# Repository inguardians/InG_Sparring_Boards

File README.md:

InG_Sparring_Boards
===================

InGuardians Sparring Boards - a collection of printed circuit boards (PCB) to help users learn about embedded devices and the tools and techniques used during development and assessment.

InGuardians<br>
http://www.inguardians.com<br>
http://labs.inguardians.com<br>

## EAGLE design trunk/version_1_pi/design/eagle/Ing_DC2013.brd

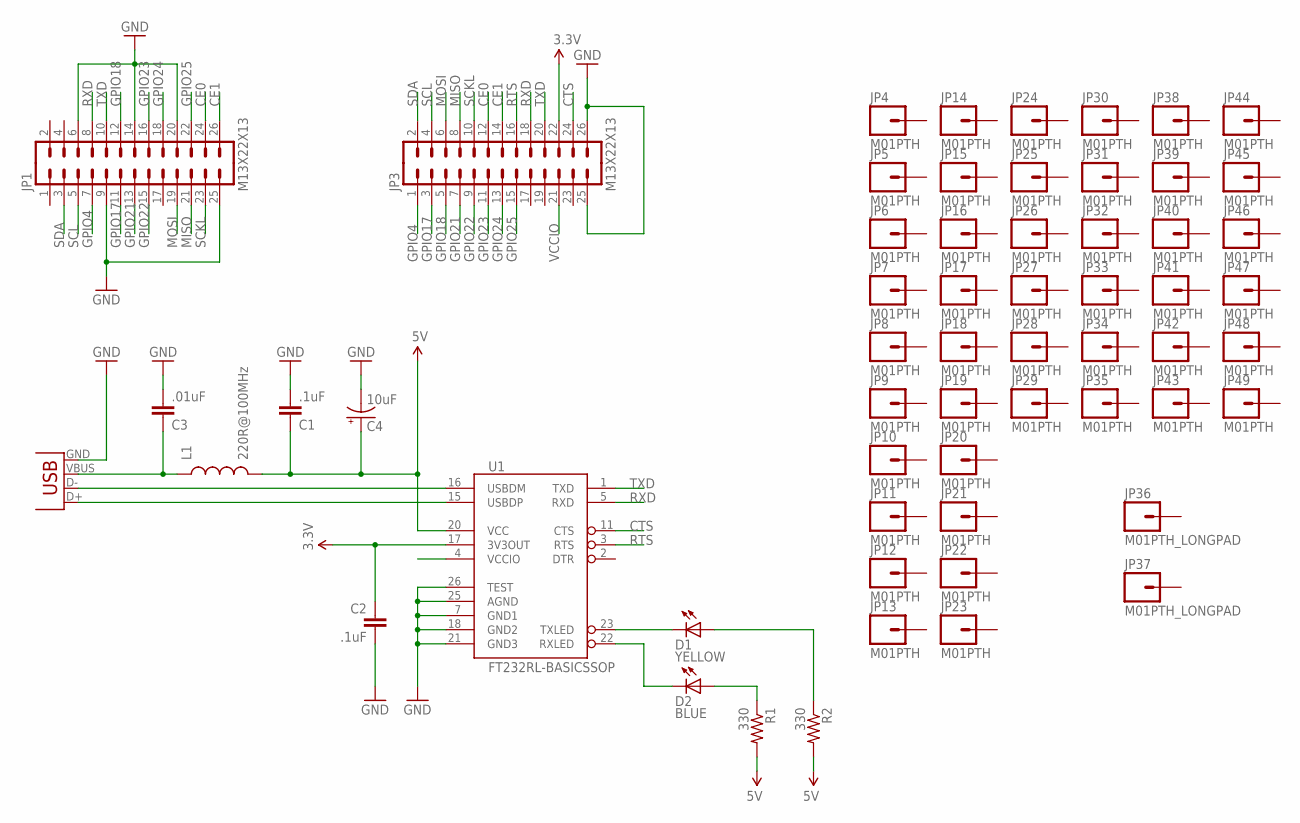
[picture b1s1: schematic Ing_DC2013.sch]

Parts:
C1, C2: .1uF; 1206
C3: .01uF; 1206
C4: 10uF; EIA3216
D1: YELLOW; LED-1206
D2: BLUE; LED-1206
JP1, JP3: M13X22X13; 2X13
JP2: USB-SMD-NS; USB-MINIB-NOSTOP
JP4, JP5, JP6, JP7, JP8, JP9, JP10, JP11, JP12, JP13, JP14, JP15, JP16, JP17, JP18, JP19, JP20, JP21, JP22, JP23, JP24, JP25, JP26, JP27, JP28, JP29, JP30, JP31, JP32, JP33, JP34, JP35, JP38, JP39, JP40, JP41, JP42, JP43, JP44, JP45, JP46, JP47, JP48, JP49: M01PTH; 1X01
JP36, JP37: M01PTH_LONGPAD; 1X01_LONGPAD
L1: 220R@100MHz; 1210
R1, R2: 330; 1206
U1: FT232RL-BASICSSOP; SSOP28DB

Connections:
3.3V: C2.1, JP3.22, U1.17 (3V3OUT)
5V: C1.1, C4.A (+), L1.2, R1.2, R2.2, U1.20 (VCC)
CE0: JP1.24, JP3.12
CE1: JP1.26, JP3.14
CTS: JP3.24, U1.11 (CTS)
GND: C1.2, C2.2, C3.2, C4.C (-), JP1.6, JP1.9, JP1.14, JP1.20, JP1.25, JP2.GND, JP3.25, JP3.26, U1.7 (GND1), U1.18 (GND2), U1.21 (GND3), U1.25 (AGND), U1.26 (TEST)
GPIO4: JP1.7, JP3.1
GPIO17: JP1.11, JP3.3
GPIO18: JP1.12, JP3.5
GPIO21: JP1.13, JP3.7
GPIO22: JP1.15, JP3.9
GPIO23: JP1.16, JP3.11
GPIO24: JP1.18, JP3.13
GPIO25: JP1.22, JP3.15
MISO: JP1.21, JP3.8
MOSI: JP1.19, JP3.6
unnamed: C3.1, JP2.VBUS, L1.1
unnamed: D2.A, R1.1
unnamed: D2.C, U1.22 (RXLED)
unnamed: D1.C, U1.23 (TXLED)
unnamed: JP2.D-, U1.16 (USBDM)
unnamed: JP2.D+, U1.15 (USBDP)
unnamed: D1.A, R2.1
RTS: JP3.16, U1.3 (RTS)
RXD: JP1.8, JP3.18, U1.5 (RXD)
SCKL: JP1.23, JP3.10
SCL: JP1.5, JP3.4
SDA: JP1.3, JP3.2
TXD: JP1.10, JP3.20, U1.1 (TXD)
VCCIO: JP3.21, U1.4 (VCCIO)

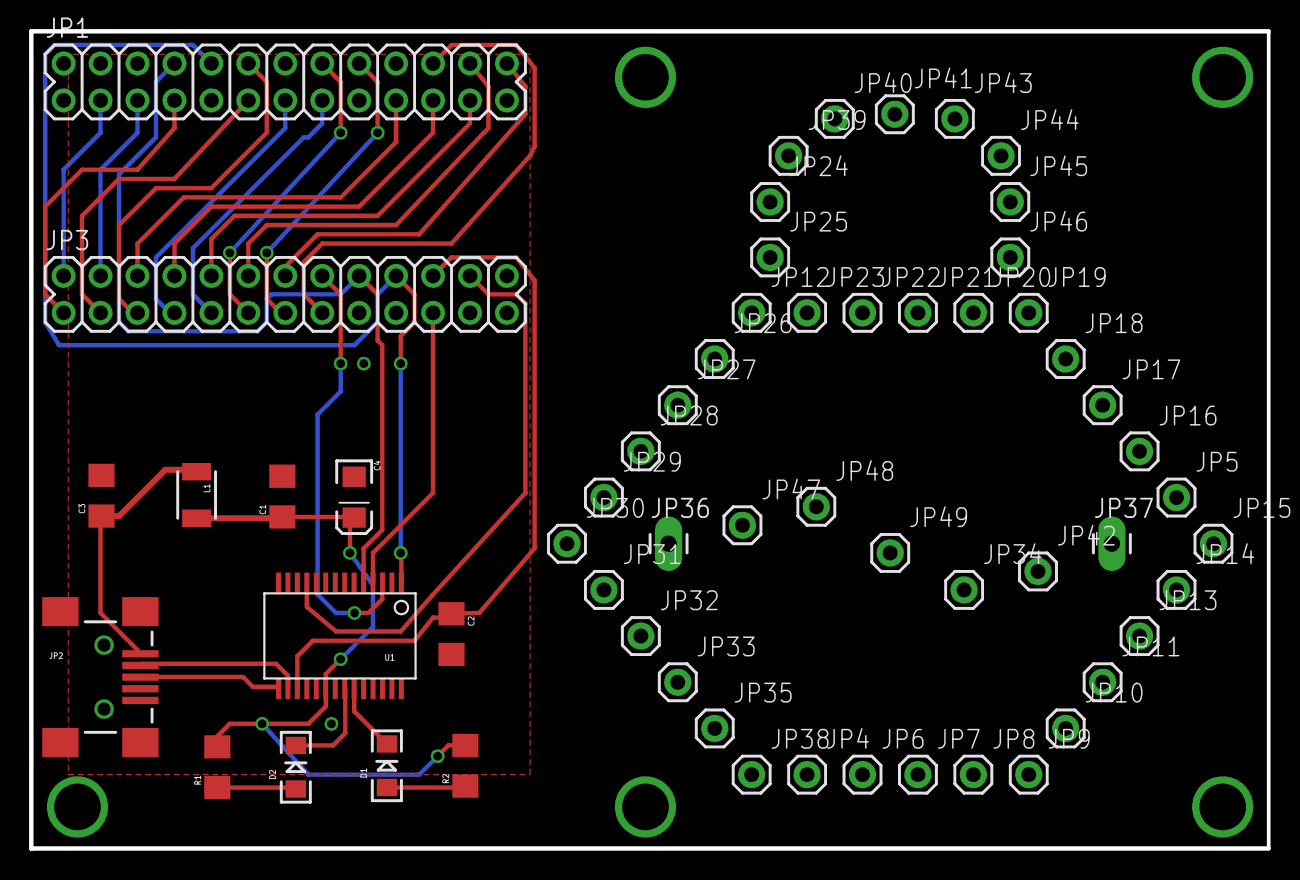
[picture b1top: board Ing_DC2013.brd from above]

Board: 2 copper layers, 85.1 x 56.2 mm, 59 parts (0 on the bottom side), 30 nets.

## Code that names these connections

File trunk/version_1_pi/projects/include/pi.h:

/*! \file pi.h
  \author Travis Goodspeed
  \modded Don C. Weber (cutaway)
  \brief Port descriptions for the PI platform. Combination of platform.h, config.h, and other configurations.
*/

#ifndef __pi
#define __pi

#ifdef __cplusplus
extern "C" {
#endif

/************************************************************
* STANDARD BITS - taken from msp430f2274.h
************************************************************/

#define BIT0                (0x0001)
#define BIT1                (0x0002)
#define BIT2                (0x0004)
#define BIT3                (0x0008)
#define BIT4                (0x0010)
#define BIT5                (0x0020)
#define BIT6                (0x0040)
#define BIT7                (0x0080)
#define BIT8                (0x0100)
#define BIT9                (0x0200)
#define BITA                (0x0400)
#define BITB                (0x0800)
#define BITC                (0x1000)
#define BITD                (0x2000)
#define BITE                (0x4000)
#define BITF                (0x8000)


/************************************************************
* SERIAL SETUP - taken from http://www.raspberry-projects.com/pi/programming-in-c/uart-serial-port/using-the-uart
************************************************************/

// Define Raspberry Pi version - default to RPv2
#ifndef RPv1
    #ifndef RPv2
    #define RPv2
    #endif
#endif

/************************************************************
* COMMANDS - temp for testing. These should be same as command.h
************************************************************/

// Global Commands
#define FLASH4  0x61 //a
#define FLASH17 0x62 //b
#define FLASH18 0x63 //c
#define FLASH27 0x64 //d
#define FLASH22 0x65 //e
#define FLASH23 0x66 //f
#define FLASH24 0x67 //g
#define FLASH25 0x68 //h
#define DONE    0x20 //space
#define ENTER   0x0a //enter

/************************************************************
* PINOUT DEFINITIONS
************************************************************/
// Access from ARM Running Linux

#define BCM2708_PERI_BASE        0x20000000
#define GPIO_BASE                (BCM2708_PERI_BASE + 0x200000) /* GPIO controller */

#define PAGE_SIZE (4*1024)
#define BLOCK_SIZE (4*1024)

// GPIO setup macros. Always use INP_GPIO(x) before using OUT_GPIO(x) or SET_GPIO_ALT(x,y)
#define GPIO_SET *(gpio+7)  // sets   bits which are 1 ignores bits which are 0
#define GPIO_CLR *(gpio+10) // clears bits which are 1 ignores bits which are 0
#define GPIO_LVL *(gpio+13) // clears bits which are 1 ignores bits which are 0

#define INP_GPIO(g) *(gpio+((g)/10)) &= ~(7<<(((g)%10)*3))
#define OUT_GPIO(g) *(gpio+((g)/10)) |=  (1<<(((g)%10)*3))
#define SET_GPIO_ALT(g,a) *(gpio+(((g)/10))) |= (((a)<=3?(a)+4:(a)==4?3:2)<<(((g)%10)*3))
#define GPIO_TGL(g) GPIO_LVL & (1<<g) ? (GPIO_CLR = 1<<g): (GPIO_SET = 1<<g);

// I/O access
int mem_fd;
void *gpio_map;
volatile unsigned *gpio;

void setup_io();

#define PIPIN0 4  //GPIO4
#define PIPIN1 17  //GPIO17
#define PIPIN2 18  //GPIO18
#ifdef RPv1
#define PIPIN3 21  //GPIO21
#else
#define PIPIN3 27  //GPIO27
#endif
#define PIPIN4 22  //GPIO22
#define PIPIN5 23  //GPIO23
#define PIPIN6 24  //GPIO24
#define PIPIN7 25  //GPIO25
#define PIPIN15 15  //UART TXD
#define PIPIN16 16  //UART RXD

//LED on P1.0
//#define PLEDOUT P1OUT
#define PLEDOUT P1OUT
#define PLEDDIR P1DIR
#define PLEDPIN BIT0

#define SPIOUT P5OUT
#define SPIDIR P5DIR
#define SPIIN  P5IN
#define SPIREN P5REN

/************************************************************
* End of Modules
************************************************************/
#ifdef __cplusplus
}
#endif /* extern "C" */

#endif/* __pi */

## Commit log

2013-07-27 cutaway - initial commit with Sparring Board v1.2
2013-07-27 cutaway - added projects
2013-07-27 cutaway - added images

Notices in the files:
parts and their libraries:
SparkFun-DigitalIC: Licensing: CC v3.0 Share-Alike You are welcome to use this library for commercial purposes.
